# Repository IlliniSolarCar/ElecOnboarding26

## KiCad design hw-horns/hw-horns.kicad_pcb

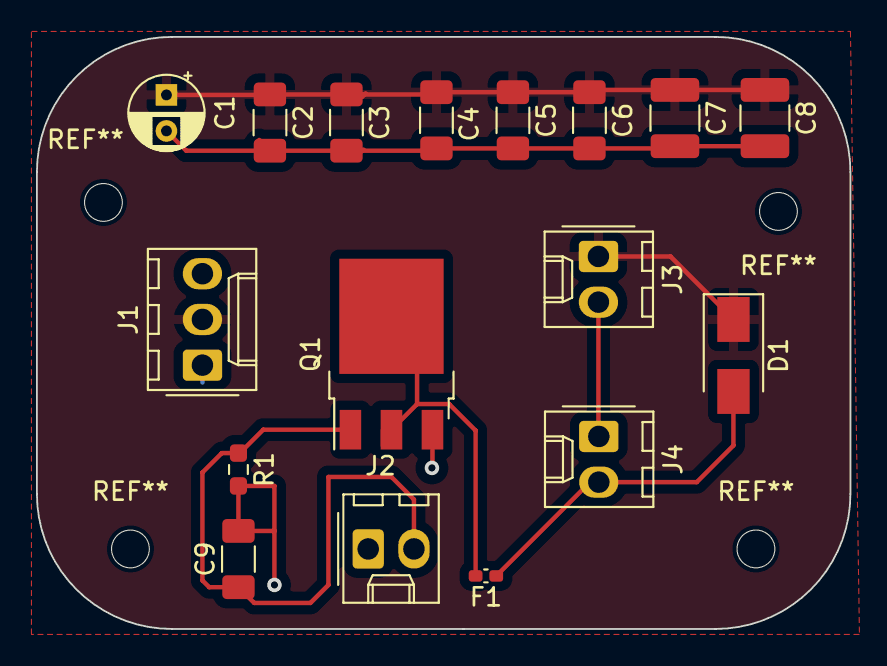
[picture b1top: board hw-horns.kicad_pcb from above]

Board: 2 copper layers, 45.2 x 32.9 mm, 17 parts (0 on the bottom side), 6 nets.

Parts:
C1: 100u; CP_Radial_D4.0mm_P2.00mm
C2, C3, C4, C9: 0.1u; C_1206_3216Metric_Pad1.33x1.80mm_HandSolder
C5, C6: 1u; C_1206_3216Metric_Pad1.33x1.80mm_HandSolder
C7, C8: 10u; C_1210_3225Metric_Pad1.33x2.70mm_HandSolder
D1: 1N4001; D_SMA
F1: Fuse; Fuse_0402_1005Metric_Pad0.77x0.64mm_HandSolder
J1: Conn_01x03_Female; Molex_KK-254_AE-6410-03A_1x03_P2.54mm_Vertical
J2: Conn_01x02_Female; Molex_KK-254_AE-6410-02A_1x02_P2.54mm_Vertical
J3, J4: Conn_01x02_Male; Molex_KK-254_AE-6410-02A_1x02_P2.54mm_Vertical
Q1: IRFS4127; TO-252-3_TabPin2
R1: 1000; R_0603_1608Metric_Pad0.98x0.95mm_HandSolder

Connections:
+24V: C1.1, C2.1, C3.1, C4.1, C5.1, C6.1, C7.1, C8.1, D1.1 (K), J1.2, J3.1
/Horn Control: C9.1, J2.2, Q1.1 (G), R1.1
/Horn In: D1.2 (A), F1.1, J4.2
GND: C1.2, C2.2, C3.2, C4.2, C5.2, C6.2, C7.2, C8.2, C9.2, J1.1, J1.3, J2.1, Q1.3 (S), R1.2
unnamed: J3.2, J4.1
unnamed: F1.2, Q1.2 (D)

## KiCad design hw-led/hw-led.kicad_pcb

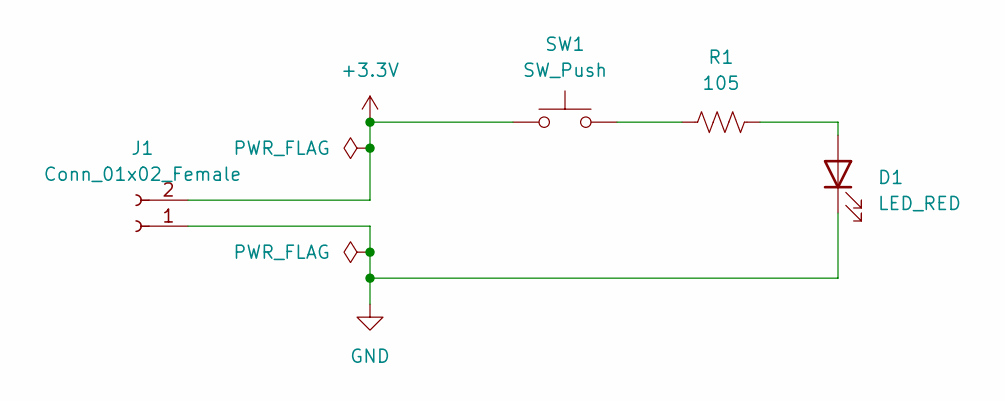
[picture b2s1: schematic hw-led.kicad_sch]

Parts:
D1: LED_RED; LED_0603_Symbol_on_F.SilkS
J1: Conn_01x02_Female; Molex_KK-254_AE-6410-02A_1x02_P2.54mm_Vertical; MPN 022272021
R1: 105; R_0603_1608Metric_Pad0.98x0.95mm_HandSolder
SW1: SW_Push; SW_DIP_SPSTx01_Slide_6.7x4.1mm_W8.61mm_P2.54mm_LowProfile; MPN 1825910-6

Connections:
+3.3V: J1.2, SW1.1
GND: D1.1 (K), J1.1
unnamed: D1.2 (A), R1.2
unnamed: R1.1, SW1.2

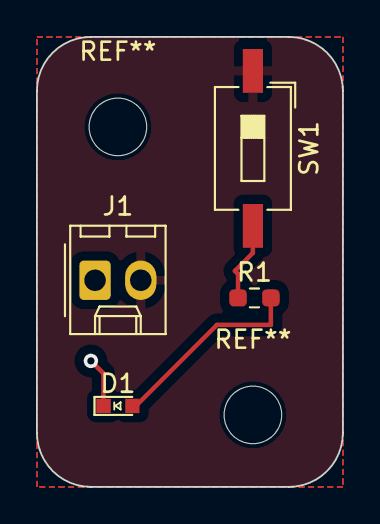
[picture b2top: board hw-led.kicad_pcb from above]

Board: 2 copper layers, 17.0 x 25.0 mm, 4 parts (0 on the bottom side), 4 nets.

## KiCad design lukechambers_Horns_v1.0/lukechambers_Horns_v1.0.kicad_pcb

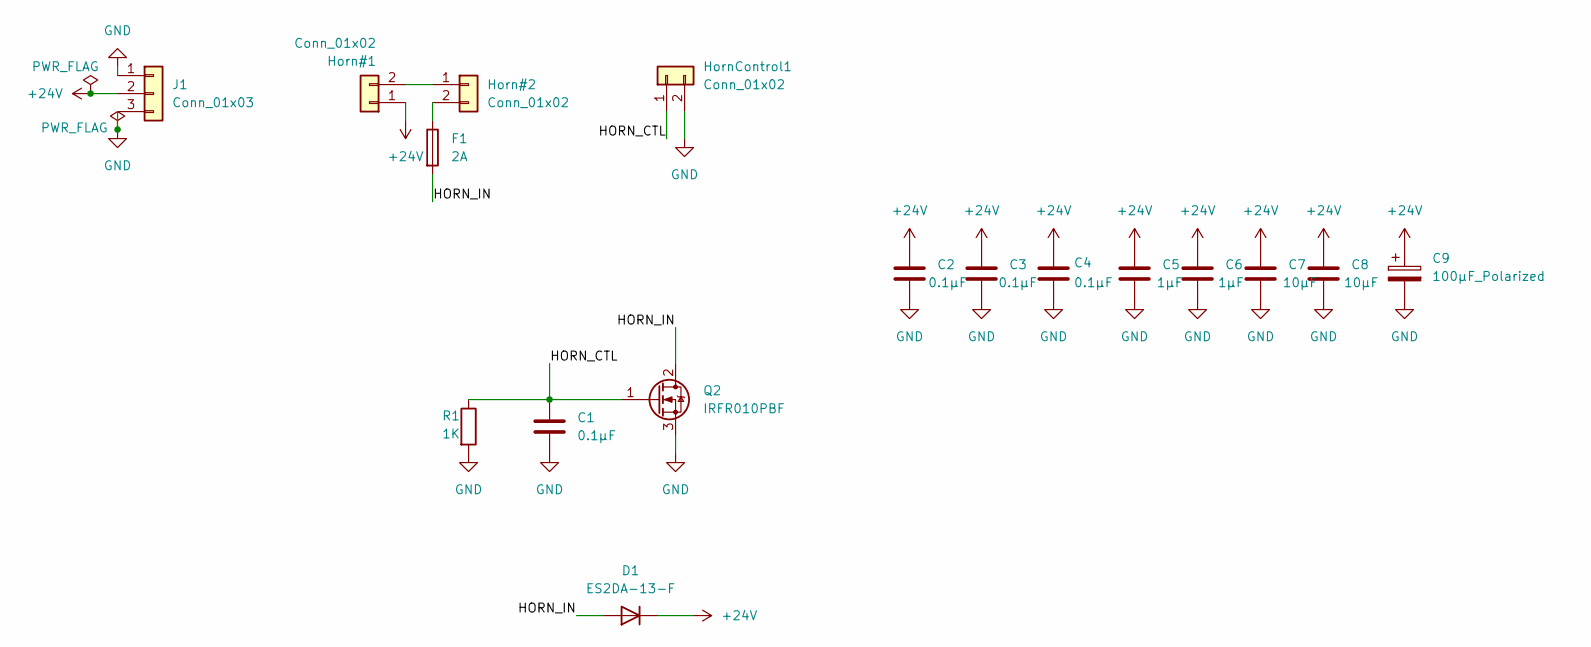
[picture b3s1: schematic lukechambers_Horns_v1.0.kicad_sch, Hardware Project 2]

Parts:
C1, C2, C3, C4: 0.1µF; C_1206_3216Metric
C5, C6: 1µF; C_1206_3216Metric
C7, C8: 10µF; C_1206_3216Metric
C9: 100µF_Polarized; CP_Radial_D8.0mm_P3.50mm
D1: ES2DA-13-F; D_SMA
F1: 2A; Fuse_1206_3216Metric
Horn#1, Horn#2: Conn_01x02; PinSocket_1x02_P2.54mm_Vertical
HornControl1: Conn_01x02; PinSocket_1x02_P2.54mm_Vertical
J1: Conn_01x03; PinSocket_1x03_P2.54mm_Vertical
Q2: IRFR010PBF; TO-252-2
R1: 1K; R_1206_3216Metric

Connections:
+24V: C2.1, C3.1, C4.1, C5.1, C6.1, C7.1, C8.1, C9.1, D1.1 (K), Horn#1.1, J1.2
/HORN_CTL: C1.1, HornControl1.1, Q2.1 (G), R1.1
/HORN_IN: D1.2 (A), F1.2, Q2.2 (D)
GND: C1.2, C2.2, C3.2, C4.2, C5.2, C6.2, C7.2, C8.2, C9.2, HornControl1.2, J1.1, J1.3, Q2.3 (S), R1.2
unnamed: Horn#1.2, Horn#2.1
unnamed: F1.1, Horn#2.2

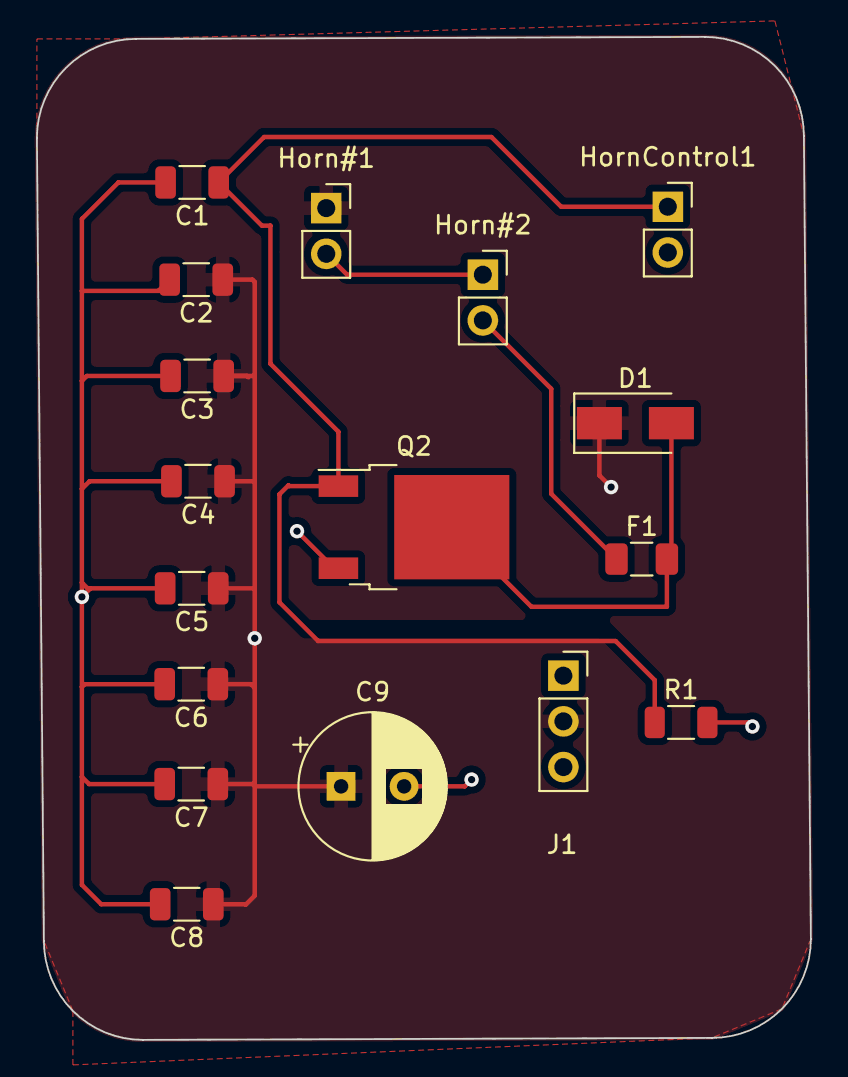
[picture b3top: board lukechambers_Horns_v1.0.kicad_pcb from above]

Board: 2 copper layers, 43.0 x 55.7 mm, 17 parts (0 on the bottom side), 6 nets.
